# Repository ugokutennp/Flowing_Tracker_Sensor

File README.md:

# Flowing_Tracker_Sensor
Sensor for SteamVR Tracking using TS4231

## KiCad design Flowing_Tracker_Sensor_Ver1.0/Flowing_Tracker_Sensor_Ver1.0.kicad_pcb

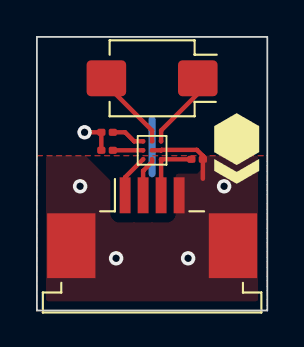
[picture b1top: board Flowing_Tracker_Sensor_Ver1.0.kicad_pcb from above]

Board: 2 copper layers, 12.8 x 15.2 mm, 6 parts (0 on the bottom side), 8 nets.

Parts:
C1: 1.0μF; C_0201_0603Metric
C2: 0.1μF; C_0201_0603Metric
D1: BPW34-SMD; Osram_SMD-DIL2_4.5x4.0mm
J1: 84953-4; TE_84953-4_1x04-1MP_P1.0mm_Horizontal
R1: 15k; R_0201_0603Metric
U1: TS4231

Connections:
GND: C1.1, C2.1, J1.4, J1.MP, R1.2, U1.5 (AVSS), U1.6 (AVSS2)
unnamed: C1.2, U1.1 (AVDD)
unnamed: C2.2, J1.3, U1.9 (DVDD)
unnamed: D1.1 (K), U1.3 (IN-)
unnamed: D1.2 (A), U1.2 (IN+)
unnamed: J1.1, U1.7 (D)
unnamed: J1.2, U1.8 (E)
unnamed: R1.1, U1.4 (RBIAS)
